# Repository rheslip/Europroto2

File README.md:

# Europroto2
 8HP Eurorack Prototyping Board for Thuhole or SMT
 
 I got tired of cutting perfboard to size and wiring up the same power supply every time I made a custom eurorack module so I designed this simple prototyping PCB. I find 8HP works very well for small projects - any more complex and I don't want to hand wire it.
 The board has a grid of holes on .1" centers which accomodates DIP packages, thruhole parts, PJ301 type jacks and 9mm pots very nicely. The power header, protection diodes, bypass and bulk decouping caps are prewired and there is a ring of GND holes around the perimeter. Adjacent to the power supply are 5 holes each for wiring +-12V. My favorite way to use this is put the chips in sockets on the panel side of the board 0603 size SMT parts on the bottom side. I use wire wrap wire to hook everything up.

 Check out my repository for gerbers of a companion 8HP FR4 blank panel. It has copper both sides for strength. You can solder some standoffs or wires to it this for attaching the protoboard if you don't have pots, jacks etc to bolt the panel to the board. It has my initials on one side but you can just turn it over or design your own with this nifty tool: https://delptronics.com/mcs-panel-maker.php

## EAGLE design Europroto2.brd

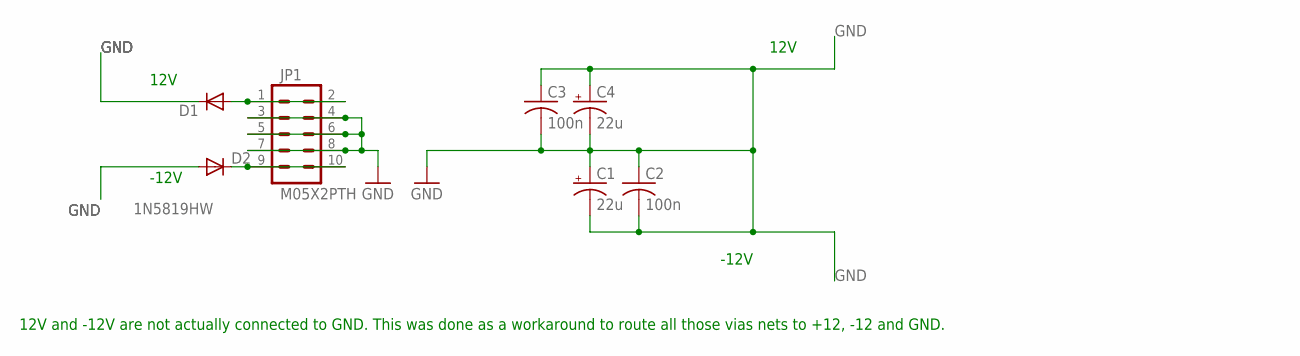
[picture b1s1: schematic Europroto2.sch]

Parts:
C1, C4: 22u; PANASONIC_B
C2, C3: 100n; C0603
D1, D2: 1N5819HW; SOD123
JP1: M05X2PTH; AVR_ICSP

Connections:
GND: C1.+, C1.-, C2.1, C2.2, C3.1, C3.2, C4.+, C4.-, D1.C, D2.A, JP1.3, JP1.4, JP1.5, JP1.6, JP1.7, JP1.8
unnamed: D1.A, JP1.1, JP1.2
unnamed: D2.C, JP1.9, JP1.10

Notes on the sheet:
12V
-12V
12V and -12V are not actually connected to GND. This was done as a workaround to route all those vias nets to +12, -12 and GND.

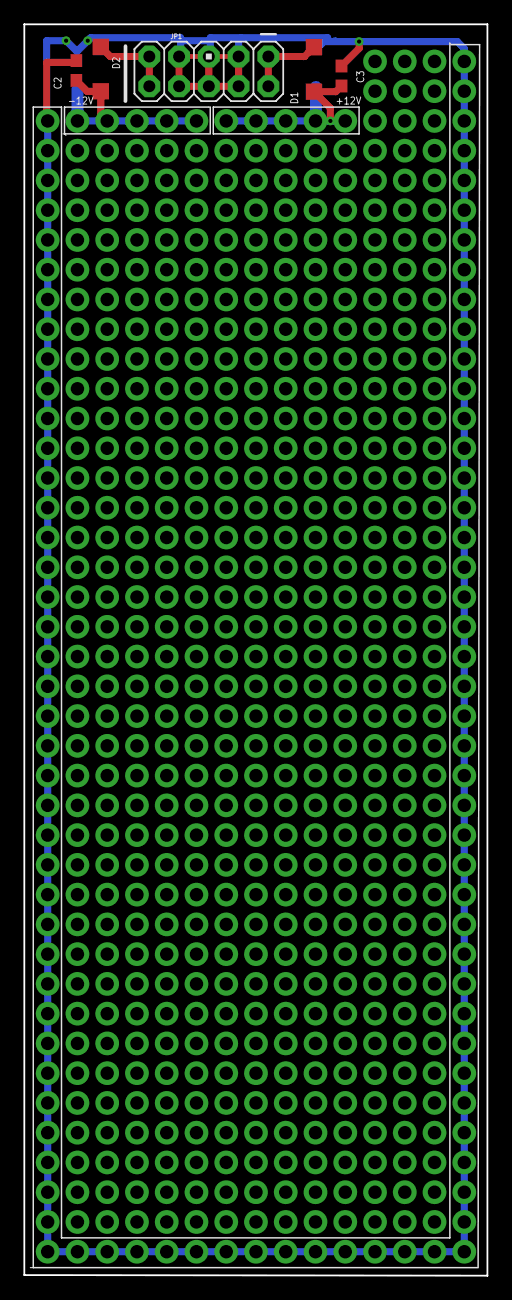
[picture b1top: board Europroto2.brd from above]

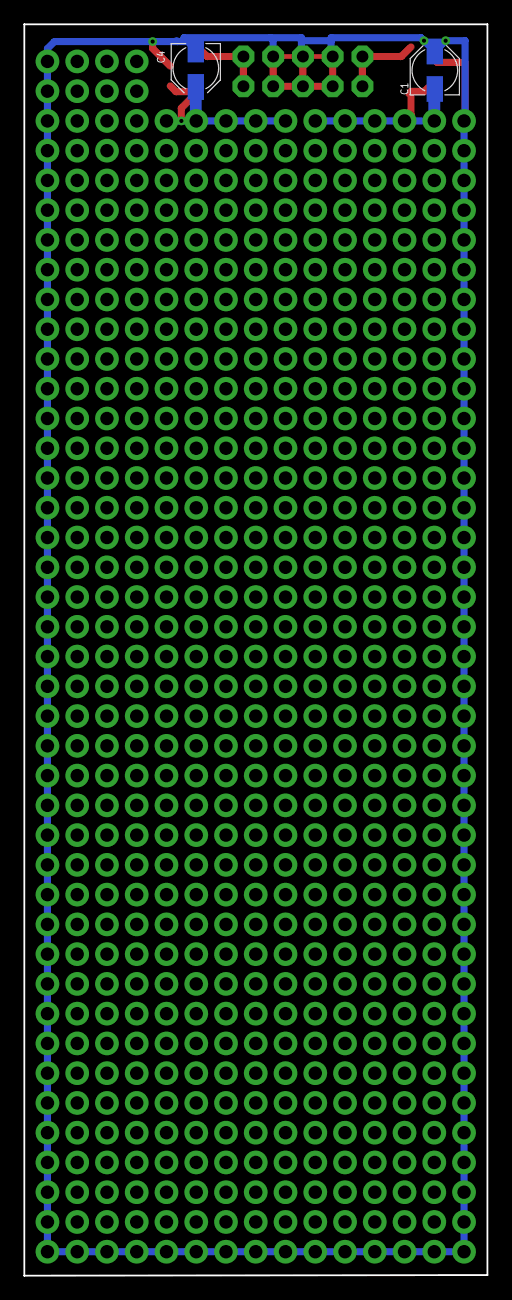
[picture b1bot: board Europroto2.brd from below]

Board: 2 copper layers, 39.5 x 106.8 mm, 7 parts (2 on the bottom side), 3 nets.

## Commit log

2020-11-18 Initial commit
    First version of the PCB, power supply is verified. The rest is your circuitry.
2020-11-18 Updated photos
    resized and renamed
